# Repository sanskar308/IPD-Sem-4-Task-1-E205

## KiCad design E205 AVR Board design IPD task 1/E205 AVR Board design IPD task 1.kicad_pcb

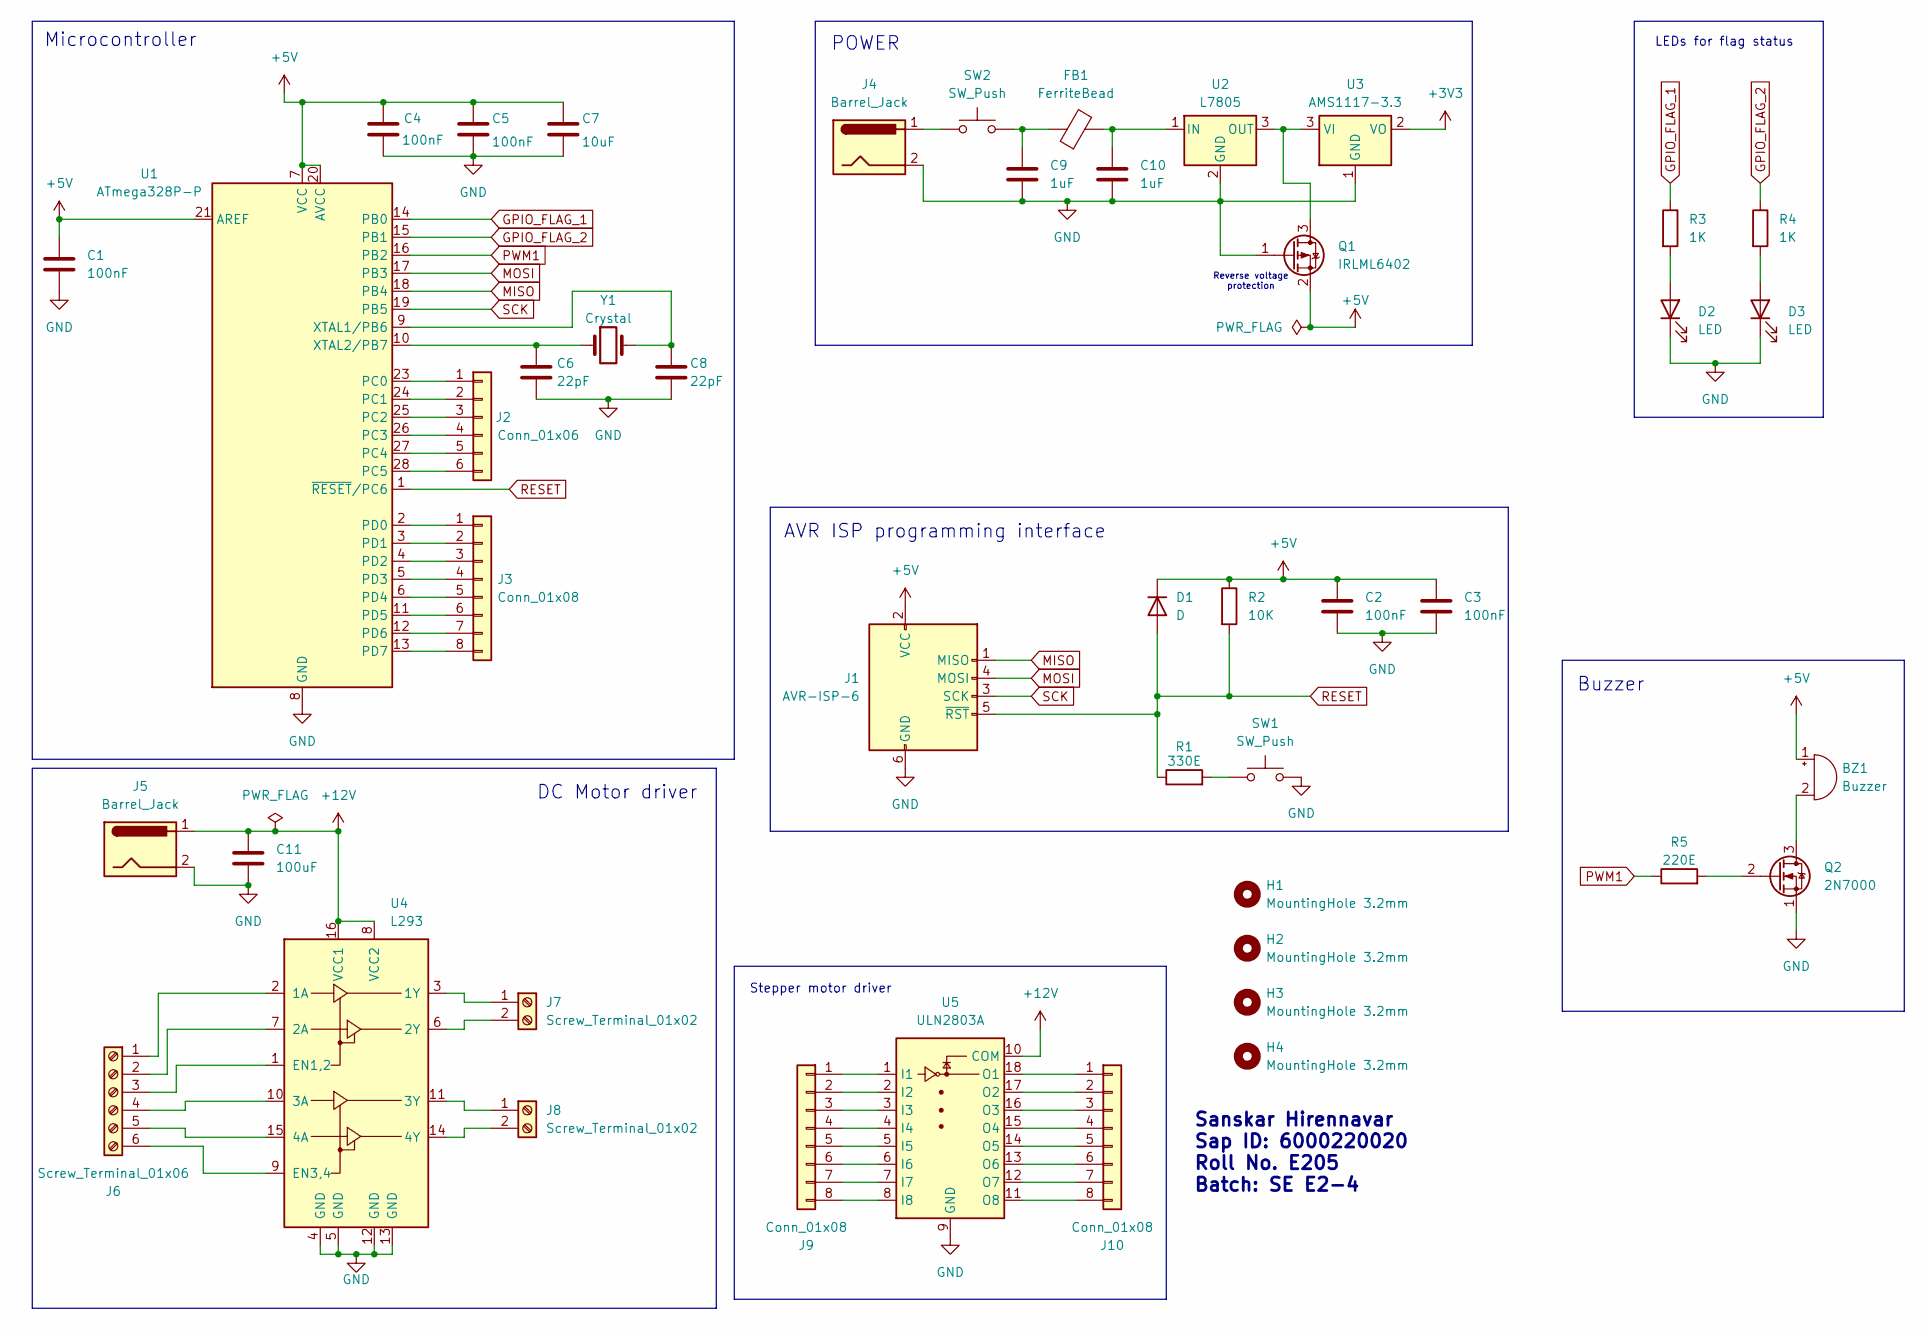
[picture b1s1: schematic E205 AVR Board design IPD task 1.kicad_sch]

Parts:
BZ1: Buzzer; Buzzer_12x9.5RM7.6
C1, C2, C3, C4, C5: 100nF; C_0805_2012Metric
C6, C8: 22pF; C_0805_2012Metric
C7: 10uF; C_0805_2012Metric
C9, C10: 1uF; C_0805_2012Metric
C11: 100uF; C_0805_2012Metric
D1: D; C_0805_2012Metric
D2, D3: LED; LED_0805_2012Metric
FB1: FerriteBead; L_0805_2012Metric
H1, H2, H3, H4: MountingHole 3.2mm; MountingHole_3.2mm_M3
J1: AVR-ISP-6; IDC-Header_2x03_P2.54mm_Vertical
J2: Conn_01x06; PinHeader_1x06_P2.54mm_Vertical
J3, J9, J10: Conn_01x08; PinHeader_1x08_P2.54mm_Vertical
J4, J5: Barrel_Jack; BarrelJack_CUI_PJ-063AH_Horizontal
J6: Screw_Terminal_01x06; TerminalBlock_Phoenix_MKDS-1-6-3.81_1x06_P3.81mm_Horizontal
J7, J8: Screw_Terminal_01x02; TerminalBlock_Phoenix_MKDS-1-2-3.81_1x02_P3.81mm_Horizontal
Q1: IRLML6402; SOT-23
Q2: 2N7000; TO-92_Inline
R1: 330E; R_0805_2012Metric
R2: 10K; R_0805_2012Metric
R3, R4: 1K; R_0805_2012Metric
R5: 220E; R_0805_2012Metric
SW1, SW2: SW_Push; SW_PUSH_6mm
U1: ATmega328P-P; DIP-28_W7.62mm
U2: L7805; TO-220-3_Vertical
U3: AMS1117-3.3; SOT-223-3_TabPin2
U4: L293; DIP-16_W7.62mm
U5: ULN2803A; DIP-18_W7.62mm
Y1: Crystal; Crystal_HC49-4H_Vertical

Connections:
+3V3: U3.2 (VO)
+5V: BZ1.1 (+), C1.1, C2.1, C3.1, C4.1, C5.1, C7.1, D1.1 (K), J1.2 (VCC), Q1.2 (S), R2.1, U1.7 (VCC), U1.20 (AVCC), U1.21 (AREF)
+12V: C11.1, J5.1, U4.8 (VCC2), U4.16 (VCC1), U5.10 (COM)
GND: C1.2, C2.2, C3.2, C4.2, C5.2, C6.2, C7.2, C8.2, C9.2, C10.2, C11.2, D2.1 (K), D3.1 (K), J1.6 (GND), J4.2, J5.2, Q1.1 (G), Q2.1 (S), SW1.2, U1.8 (GND), U1.22 (GND), U2.2 (GND), U3.1 (GND), U4.4 (GND), U4.5 (GND), U4.12 (GND), U4.13 (GND), U5.9 (GND)
GPIO_FLAG_1: R3.1, U1.14 (PB0)
GPIO_FLAG_2: R4.1, U1.15 (PB1)
MISO: J1.1 (MISO), U1.18 (PB4)
MOSI: J1.4 (MOSI), U1.17 (PB3)
unnamed: BZ1.2 (-), Q2.3 (D)
unnamed: C9.1, FB1.1, SW2.2
unnamed: D2.2 (A), R3.2
unnamed: D3.2 (A), R4.2
unnamed: J2.1, U1.23 (PC0)
unnamed: J2.2, U1.24 (PC1)
unnamed: J2.3, U1.25 (PC2)
unnamed: J2.4, U1.26 (PC3)
unnamed: J2.5, U1.27 (PC4)
unnamed: J2.6, U1.28 (PC5)
unnamed: J3.1, U1.2 (PD0)
unnamed: J3.2, U1.3 (PD1)
unnamed: J3.3, U1.4 (PD2)
unnamed: J3.4, U1.5 (PD3)
unnamed: J3.5, U1.6 (PD4)
unnamed: J3.6, U1.11 (PD5)
unnamed: J3.7, U1.12 (PD6)
unnamed: J3.8, U1.13 (PD7)
unnamed: J4.1, SW2.1
unnamed: J6.1, U4.2 (1A)
unnamed: J6.2, U4.7 (2A)
unnamed: J6.3, U4.1 (EN1,2)
unnamed: J6.4, U4.10 (3A)
unnamed: J6.5, U4.15 (4A)
unnamed: J6.6, U4.9 (EN3,4)
unnamed: J7.1, U4.3 (1Y)
unnamed: J7.2, U4.6 (2Y)
unnamed: J8.1, U4.11 (3Y)
unnamed: J8.2, U4.14 (4Y)
unnamed: J9.1, U5.1 (I1)
unnamed: J9.2, U5.2 (I2)
unnamed: J9.3, U5.3 (I3)
unnamed: J9.4, U5.4 (I4)
unnamed: J9.5, U5.5 (I5)
unnamed: J9.6, U5.6 (I6)
unnamed: J9.7, U5.7 (I7)
unnamed: J9.8, U5.8 (I8)
unnamed: J10.1, U5.18 (O1)
unnamed: J10.2, U5.17 (O2)
unnamed: J10.3, U5.16 (O3)
unnamed: J10.4, U5.15 (O4)
unnamed: J10.5, U5.14 (O5)
unnamed: J10.6, U5.13 (O6)
unnamed: J10.7, U5.12 (O7)
unnamed: J10.8, U5.11 (O8)
unnamed: Q1.3 (D), U2.3 (OUT), U3.3 (VI)
unnamed: Q2.2 (G), R5.2
unnamed: R1.2, SW1.1
unnamed: C8.1, U1.9 (XTAL1/PB6), Y1.2
unnamed: C6.1, U1.10 (XTAL2/PB7), Y1.1
unnamed: C10.1, FB1.2, U2.1 (IN)
PWM1: R5.1, U1.16 (PB2)
RESET: D1.2 (A), J1.5 (~RST), R1.1, R2.2, U1.1 (~RESET/PC6)
SCK: J1.3 (SCK), U1.19 (PB5)

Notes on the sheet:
Reverse voltage protection
DC Motor driver
POWER
Microcontroller
Buzzer
Stepper motor driver
LEDs for flag status
Sanskar Hirennavar Sap ID: 6000220020 Roll No. E205 Batch: SE E2-4
AVR ISP programming interface

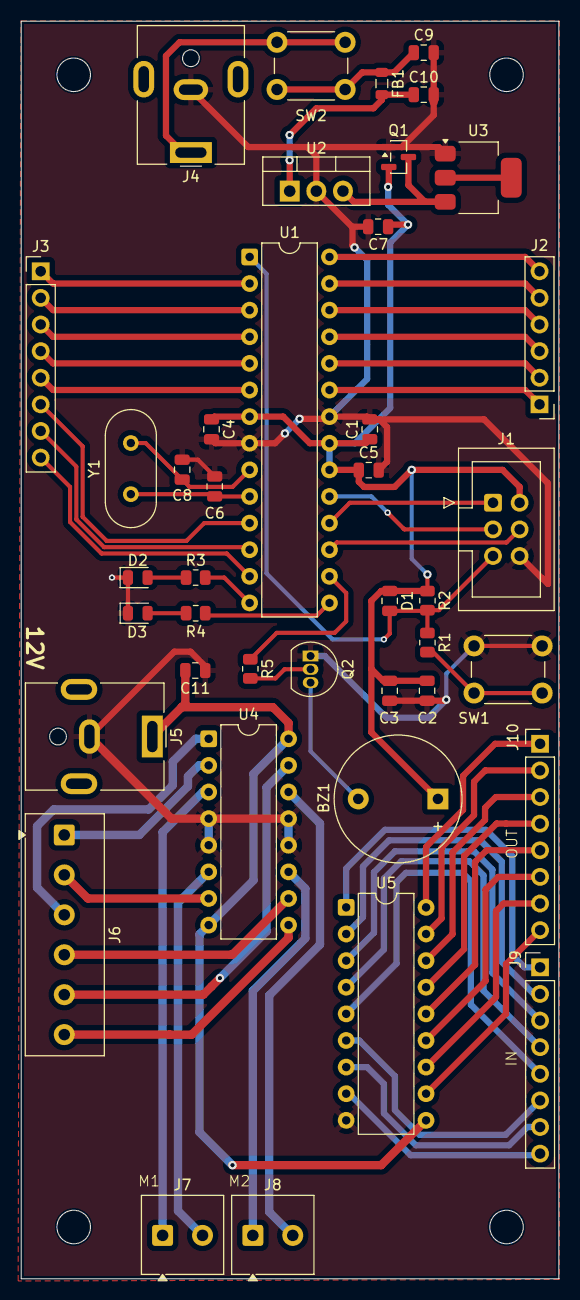
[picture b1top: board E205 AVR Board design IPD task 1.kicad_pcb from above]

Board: 2 copper layers, 51.3 x 120.0 mm, 45 parts (0 on the bottom side), 61 nets.
